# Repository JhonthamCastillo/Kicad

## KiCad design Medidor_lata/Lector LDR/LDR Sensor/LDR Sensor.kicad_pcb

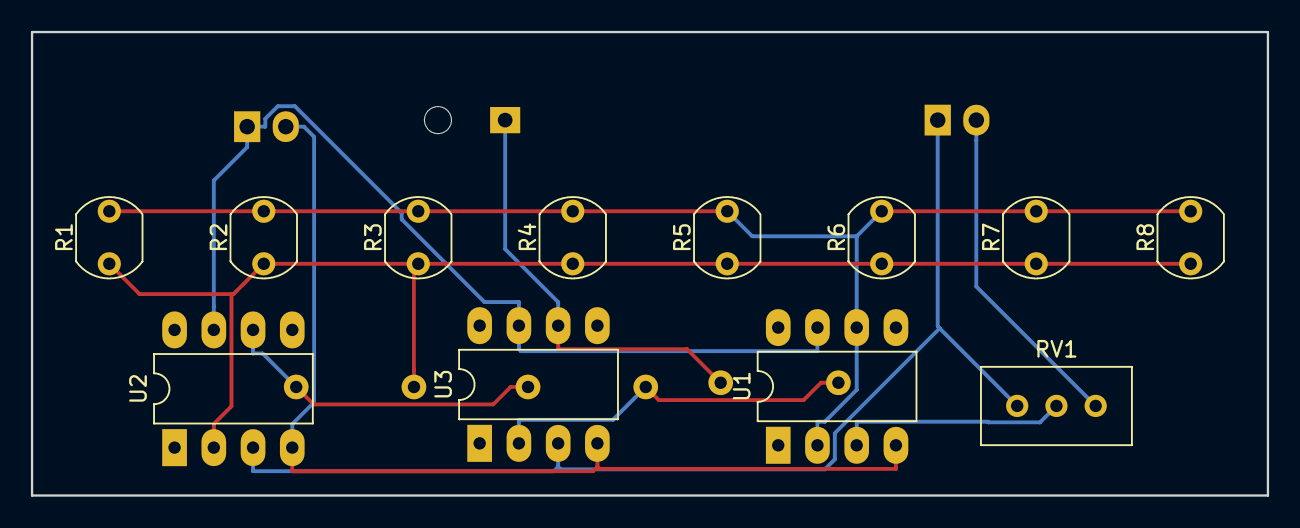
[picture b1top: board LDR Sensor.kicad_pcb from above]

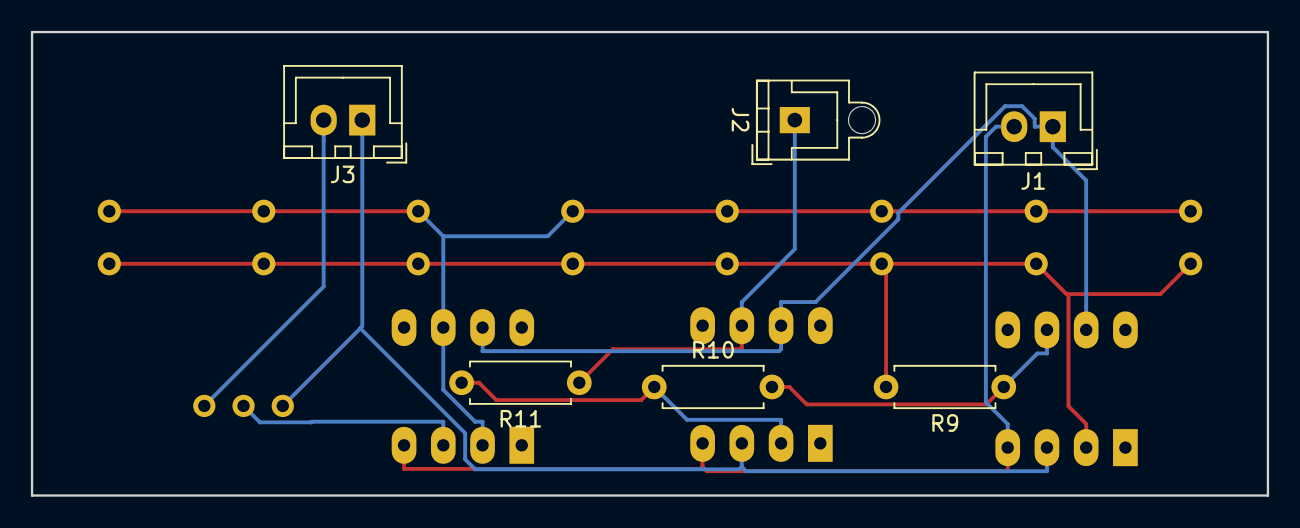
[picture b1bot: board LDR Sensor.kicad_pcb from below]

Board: 2 copper layers, 80.0 x 30.0 mm, 18 parts (6 on the bottom side), 10 nets.

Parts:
J1, J3: Conn_01x02_Female; JST_XH_B02B-XH-A_1x02_P2.50mm_Vertical
J2: Conn_01x01_Female; JST_XH_B01B-XH-AM_1x01_P2.50mm_Vertical
R1, R2, R3, R4, R5, R6, R7, R8: LDR03; R_LDR_5.1x4.3mm_P3.4mm_Vertical
R9: 1K; R_Axial_DIN0207_L6.3mm_D2.5mm_P7.62mm_Horizontal
R10, R11: 10k; R_Axial_DIN0207_L6.3mm_D2.5mm_P7.62mm_Horizontal
RV1: R_POT; Potentiometer_Bourns_3296W_Vertical
U1, U2, U3: LM741; DIP-8_W7.62mm_LongPads

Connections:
+3.7V: J3.2, RV1.1
-VCC: J1.2, U1.4, U2.4, U3.4
GND: J3.1, RV1.3, U2.3, U3.3
unnamed: J2.1, R11.1, U3.6
unnamed: R1.1, R2.1, R3.1, R4.1, R5.1, R6.1, R7.1, R8.1, R9.2, U2.2
unnamed: R1.2, R2.2, R3.2, R4.2, R5.2, R6.2, R7.2, R8.2, U1.2, U1.6
unnamed: R10.1, R11.2, U3.2
unnamed: R9.1, R10.2, U2.6
unnamed: RV1.2, U1.3
VCC: J1.1, U1.7, U2.7, U3.7

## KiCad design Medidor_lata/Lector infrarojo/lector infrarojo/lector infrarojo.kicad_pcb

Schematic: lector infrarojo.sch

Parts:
IF1, IF2, IF3, IF4, IF5, IF6, IF7: TCRT5000
J1, J2: Conn_01x02_Female; JST_XH_B03B-XH-AM_1x03_P2.50mm_Vertical
Q1, Q2, Q3, Q4, Q5, Q6, Q7: BC857; SOT-23
R1, R2, R3, R4, R5, R6, R7, R8, R9, R10, R11, R12, R13, R14, R15, R16, R17, R18, R19, R20, R21: R; R_0805_2012Metric

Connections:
unnamed: IF1.1, R1.2
unnamed: IF1.2, Q1.1 (B), R8.1
unnamed: IF1.3, IF1.4, IF2.3, IF2.4, IF3.3, IF3.4, IF4.3, IF4.4, IF5.3, IF5.4, IF6.3, IF6.4, IF7.3, IF7.4, J1.1, J2.1, R4.1, R5.1, R6.1, R7.1
unnamed: IF2.1, R2.2
unnamed: IF2.2, Q2.1 (B), R10.1
unnamed: IF3.1, R3.2
unnamed: IF3.2, Q3.1 (B), R12.1
unnamed: IF4.1, R4.2
unnamed: IF4.2, Q4.1 (B), R14.1
unnamed: IF5.1, R5.2
unnamed: IF5.2, Q5.1 (B), R16.1
unnamed: IF6.1, R6.2
unnamed: IF6.2, Q6.1 (B), R18.1
unnamed: IF7.1, R7.2
unnamed: IF7.2, Q7.1 (B), R20.1
unnamed: J1.2, J2.2, Q1.2 (E), Q2.2 (E), Q3.2 (E), Q4.2 (E), Q5.2 (E), Q6.2 (E), Q7.2 (E), R1.1, R2.1, R3.1, R8.2, R10.2, R12.2, R14.2, R16.2, R18.2, R20.2
unnamed: Q1.3 (C), R9.1
unnamed: Q2.3 (C), R11.1
unnamed: Q3.3 (C), R13.1
unnamed: Q4.3 (C), R15.1
unnamed: Q5.3 (C), R17.1
unnamed: Q6.3 (C), R19.1
unnamed: Q7.3 (C), R21.1
unnamed: R9.2, R11.2, R13.2, R15.2, R17.2, R19.2, R21.2

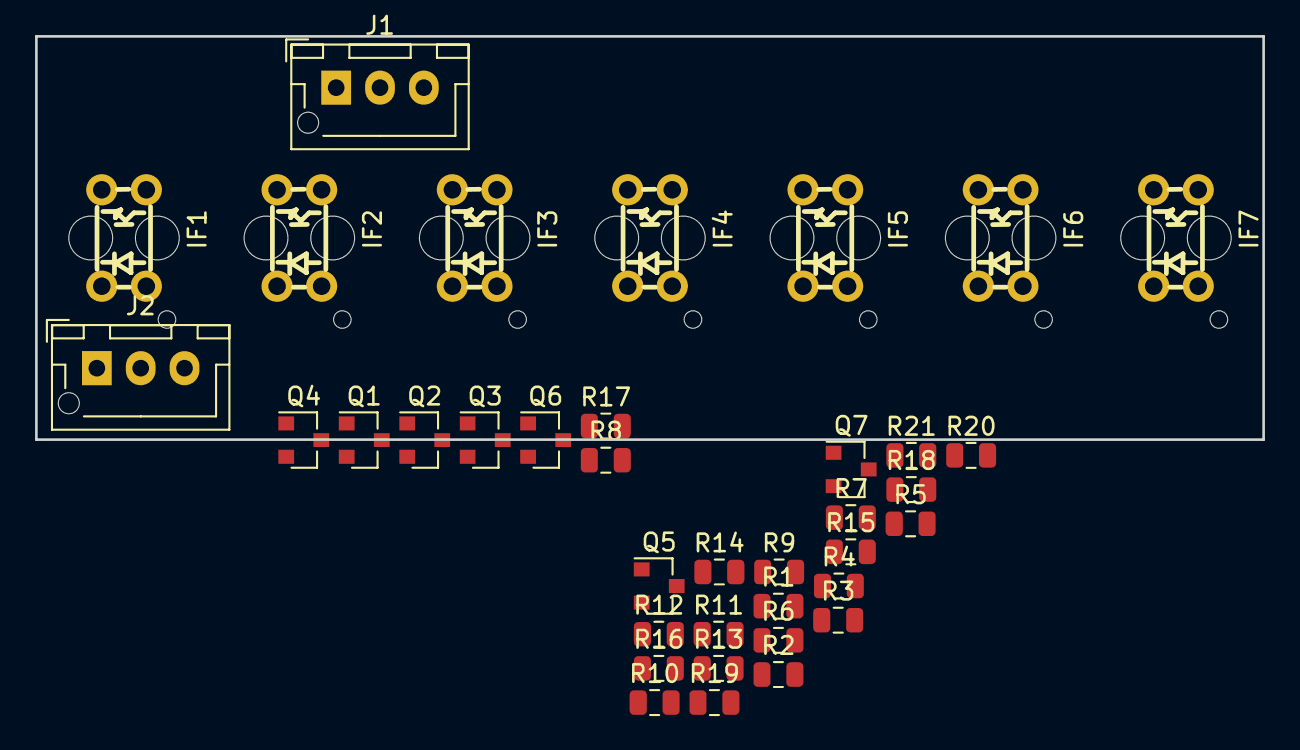
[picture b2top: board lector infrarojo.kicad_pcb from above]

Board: 2 copper layers, 70.0 x 23.0 mm, 37 parts (0 on the bottom side), 24 nets, no tracks yet.

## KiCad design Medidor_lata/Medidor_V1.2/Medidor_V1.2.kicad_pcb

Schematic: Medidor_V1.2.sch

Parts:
J1: Conn_01x02_Female; JST_EH_B02B-EH-A_1x02_P2.50mm_Vertical
J2: Conn_01x04_Female; JST_EH_B04B-EH-A_1x04_P2.50mm_Vertical
R1, R2, R3, R4, R5, R6, R7, R8, R9: R; R_0805_2012Metric
Sw1: Pulsador
U1: CC56-12EWA; 7segdisp8.0in4Dig
U2: ATmega328-AU; TQFP-32_7x7mm_P0.8mm

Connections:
+5V: J1.2, J2.1, R9.1, U2.4 (VCC), U2.6 (VCC)
GND: J1.1, J2.2, Sw1.2, U2.3 (GND), U2.5 (GND), U2.21 (GND)
unnamed: J2.3, U2.30 (PD0)
unnamed: J2.4, U2.31 (PD1)
unnamed: R1.1, U1.11
unnamed: R1.2, U2.16 (PB4)
unnamed: R2.1, U1.7
unnamed: R2.2, U2.17 (PB5)
unnamed: R3.1, U1.4
unnamed: R3.2, U2.32 (PD2)
unnamed: R4.1, U1.2
unnamed: R4.2, U2.1 (PD3)
unnamed: R5.1, U1.1
unnamed: R5.2, U2.2 (PD4)
unnamed: R6.1, U1.10
unnamed: R6.2, U2.9 (PD5)
unnamed: R7.1, U1.5
unnamed: R7.2, U2.10 (PD6)
unnamed: R8.1, U1.3
unnamed: R8.2, U2.11 (PD7)
unnamed: R9.2, Sw1.1, U2.29 (~RESET~/PC6)
unnamed: U1.6, U2.15 (PB3)
unnamed: U1.8, U2.14 (PB2)
unnamed: U1.9, U2.13 (PB1)
unnamed: U1.12, U2.12 (PB0)

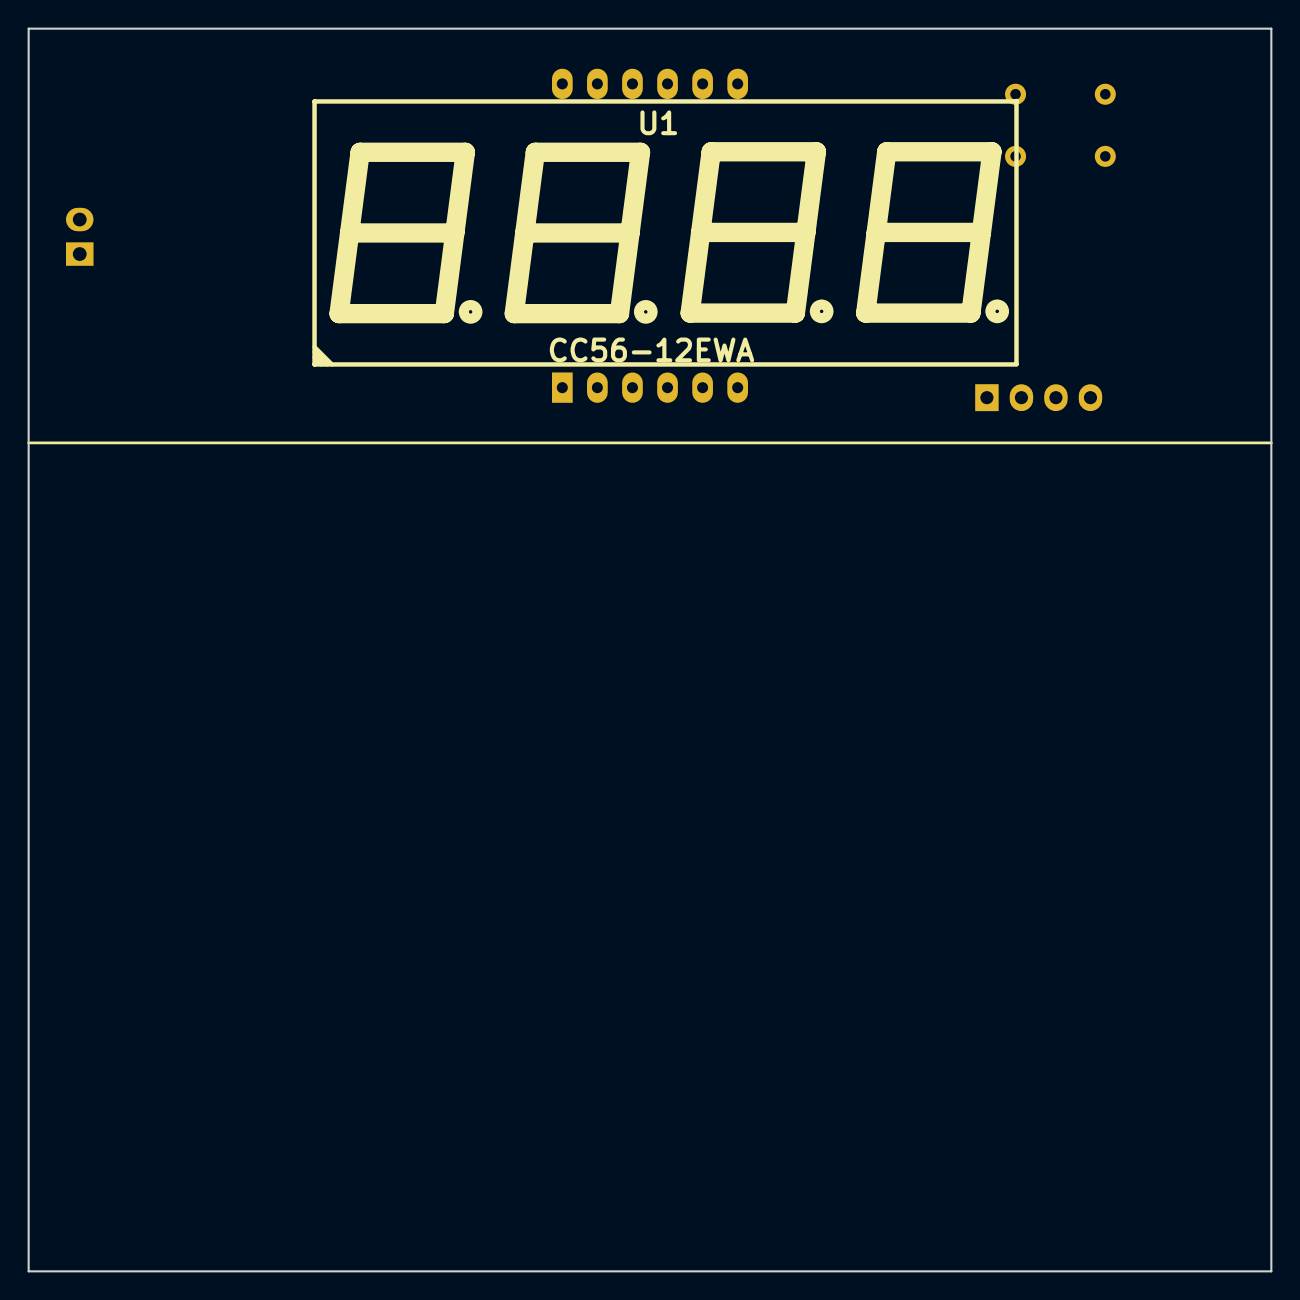
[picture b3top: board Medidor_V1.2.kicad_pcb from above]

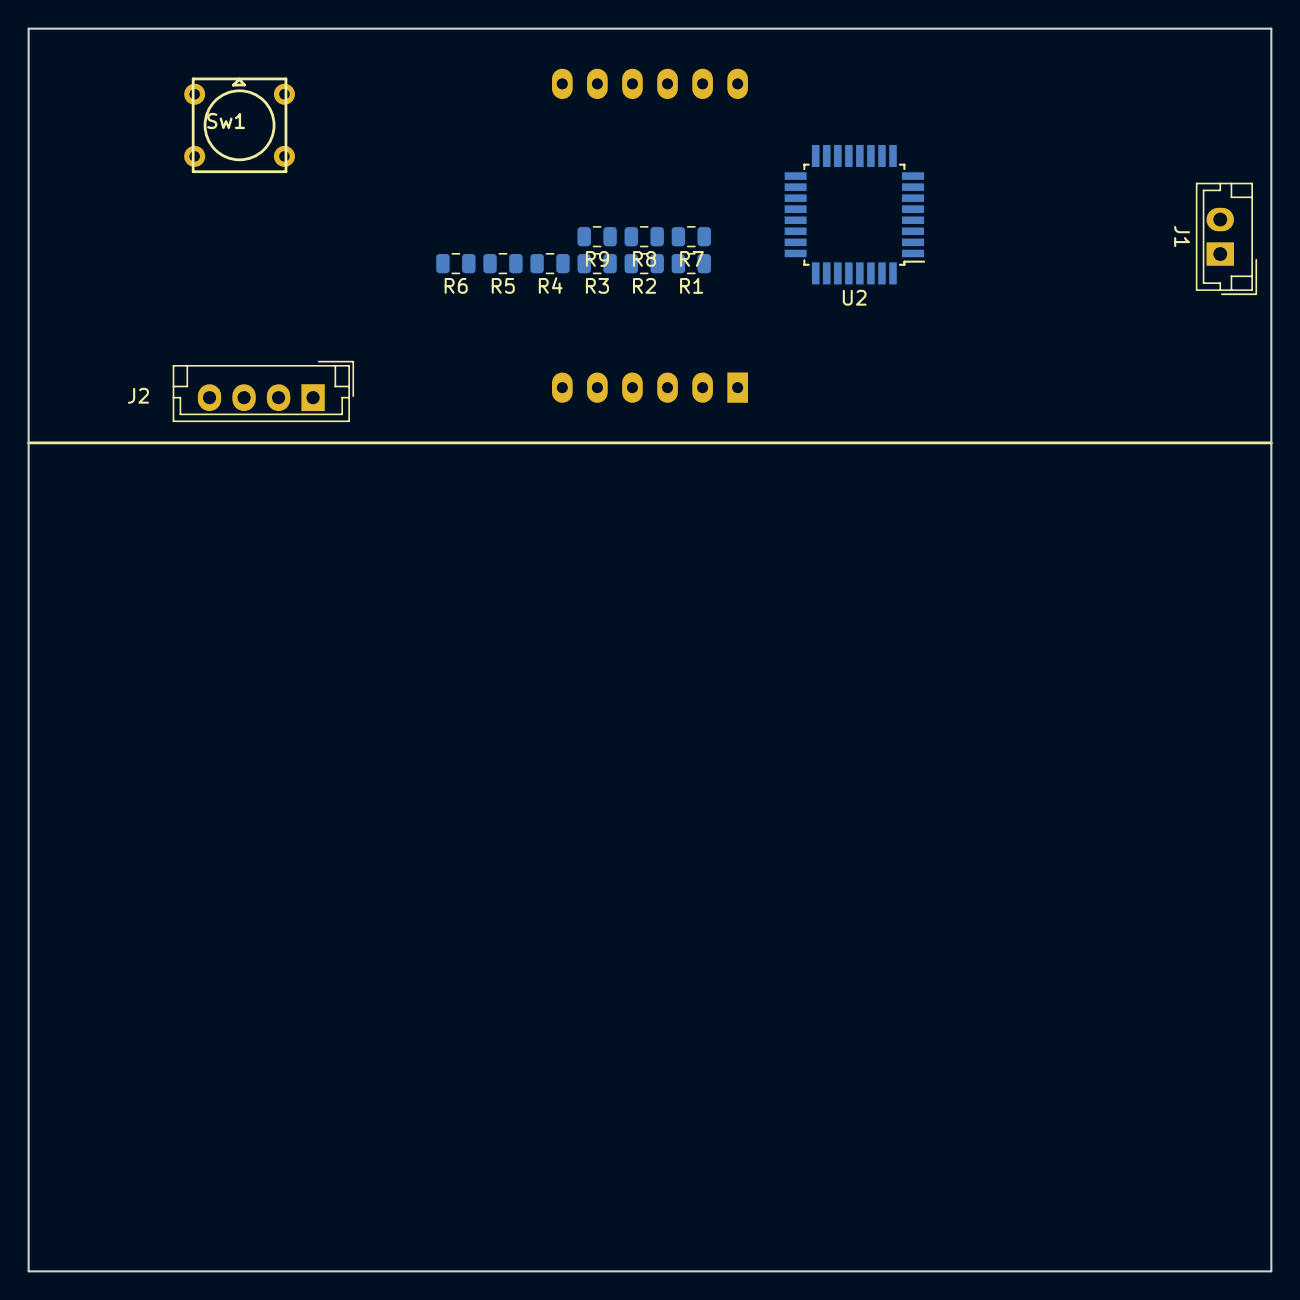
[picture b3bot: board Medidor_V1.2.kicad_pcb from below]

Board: 2 copper layers, 90.0 x 90.0 mm, 14 parts (13 on the bottom side), 25 nets, no tracks yet.

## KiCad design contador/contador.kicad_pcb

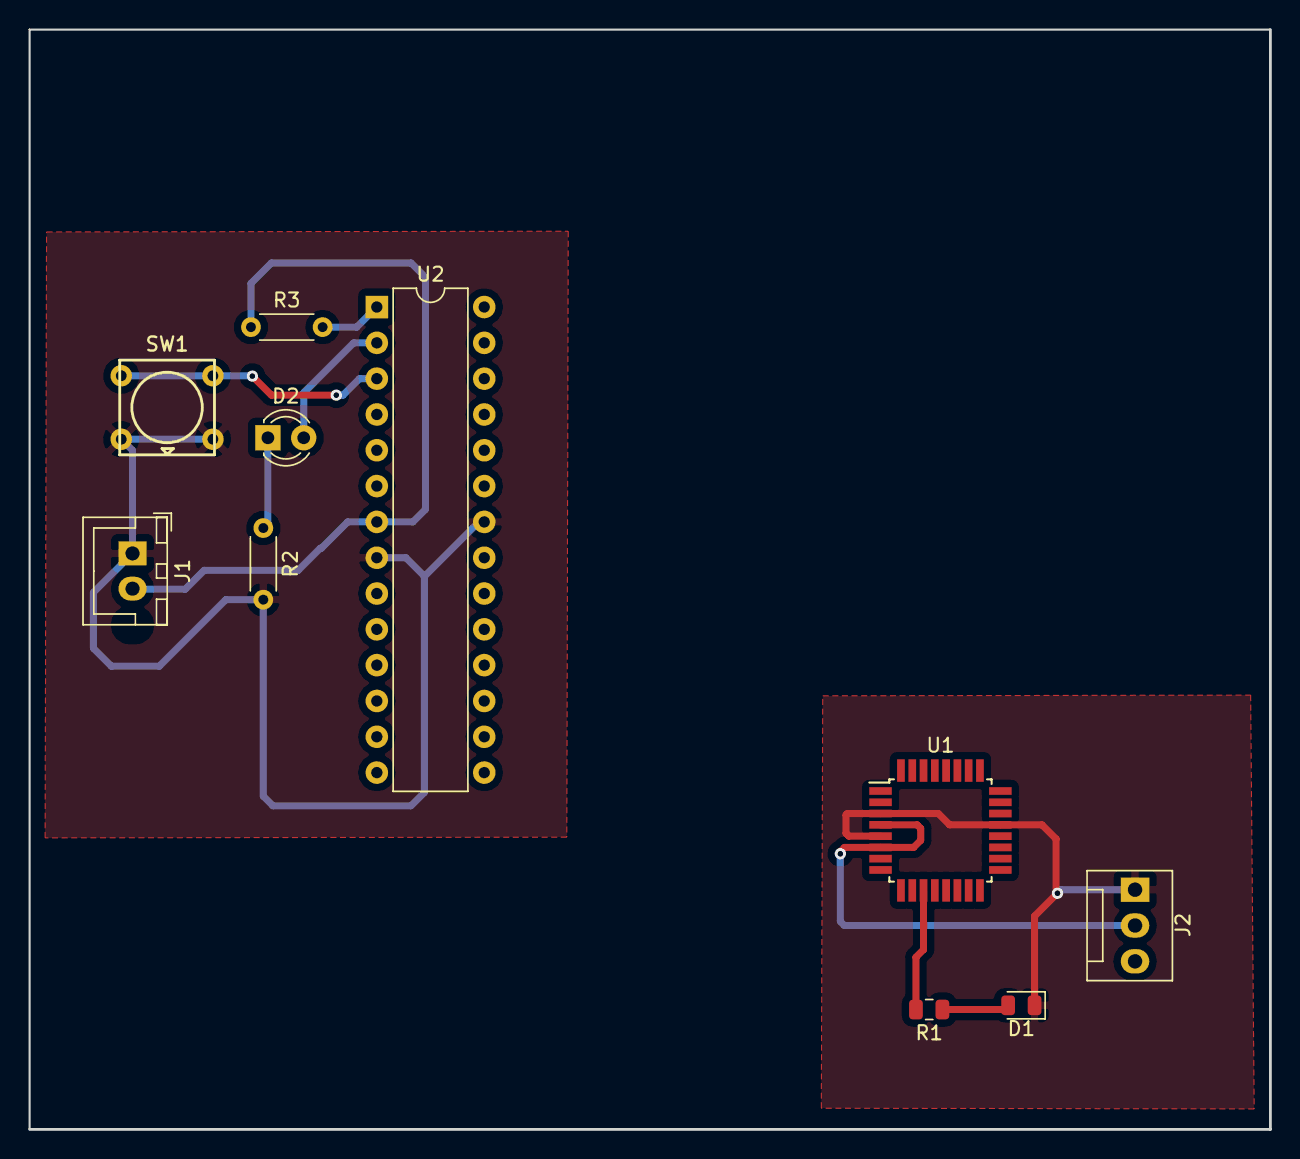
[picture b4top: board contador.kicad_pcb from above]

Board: 2 copper layers, 88.0 x 78.0 mm, 10 parts (0 on the bottom side), 8 nets.

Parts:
D1: LED; LED_0805_2012Metric
D2: LED; LED_D3.0mm
J1: Conn_01x02_Female; JST_XH_B02B-XH-A_1x02_P2.50mm_Vertical
J2: Conn_01x02_Female; FanPinHeader_1x03_P2.54mm_Vertical
R1: 361; R_0805_2012Metric
R2: 360; R_Axial_DIN0204_L3.6mm_D1.6mm_P5.08mm_Horizontal
R3: 1k; R_Axial_DIN0204_L3.6mm_D1.6mm_P5.08mm_Horizontal
SW1: Pulsador
U1: ATmega328-AU; TQFP-32_7x7mm_P0.8mm
U2: ATmega328-PU; DIP-28_W7.62mm

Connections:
+5V: J1.2, J2.2, R3.1, U1.4, U1.6, U2.7
GND: D1.1, J1.1, J2.1, R2.2, SW1.1, U1.3, U1.5, U1.21, U2.8, U2.22
unnamed: D1.2, R1.1
unnamed: D2.1, R2.1
unnamed: D2.2, U2.2
unnamed: R1.2, U1.11
unnamed: R3.2, U2.1
unnamed: SW1.2, U2.3

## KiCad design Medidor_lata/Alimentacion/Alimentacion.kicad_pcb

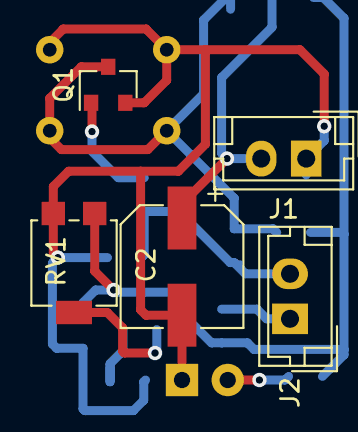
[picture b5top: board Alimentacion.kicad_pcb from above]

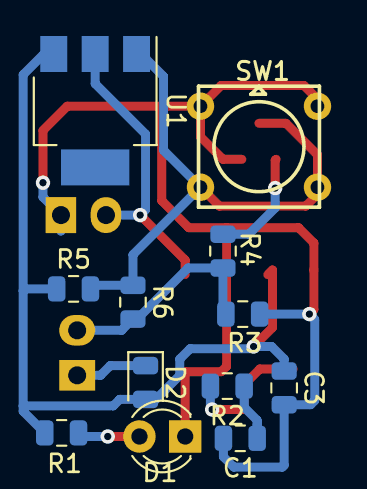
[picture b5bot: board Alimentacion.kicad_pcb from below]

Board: 2 copper layers, 17 parts (12 on the bottom side), 10 nets.

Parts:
C1, C3: C; C_0805_2012Metric
C2: CP; CP_Elec_6.3x7.7
D1: LED; LED_D3.0mm
D2: 1N4001; D_0805_2012Metric
J1, J2: Conn_01x02_Female; JST_EH_B02B-EH-A_1x02_P2.50mm_Vertical
Q1: BC847; SOT-23
R1, R2, R3, R4, R5, R6: R; R_0805_2012Metric
RV1: R_POT; Potentiometer_Bourns_3314G_Vertical
SW1: Pulsador
U1: LM317_TO3; SOT-223

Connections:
GND: C1.2, C2.2, C3.2, D1.1, J1.1, Q1.2, R3.2, RV1.3, SW1.1
unnamed: C1.1, R2.1
unnamed: C2.1, J1.2, U1.2
unnamed: C3.1, D2.2, R1.1, R5.1, RV1.1, U1.3
unnamed: D1.2, R1.2
unnamed: D2.1, J2.1
unnamed: J2.2, R3.1, R4.2, R6.2
unnamed: Q1.1, R4.1
unnamed: Q1.3, R5.2, R6.1, SW1.2, U1.1
unnamed: R2.2, RV1.2

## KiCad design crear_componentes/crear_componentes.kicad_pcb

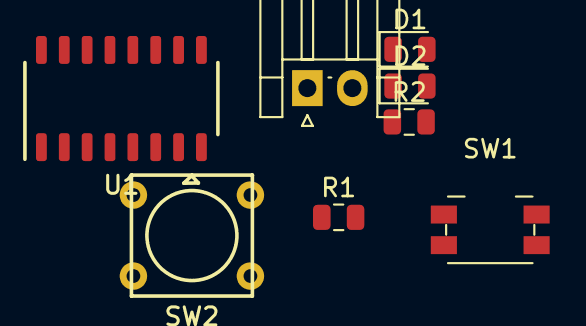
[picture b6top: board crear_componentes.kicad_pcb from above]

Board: 2 copper layers, 8 parts (0 on the bottom side), 7 nets, no tracks yet.

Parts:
D1, D2: LED; LED_0805_2012Metric
J1: Conn_01x02_Female; JST_EH_S02B-EH_1x02_P2.50mm_Horizontal
R1, R2: R; R_0805_2012Metric
SW1: SW_Push; Panasonic_EVQPUK_EVQPUB
SW2: TopPush
U1: ULN2003A; SOIC127P620X175-16

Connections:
+5V: J1.1, SW1.1, SW2.1, U1.8
GND: J1.2, R1.2, R2.2, U1.9
unnamed: D1.1, U1.16
unnamed: D1.2, R1.1
unnamed: D2.1, SW2.2
unnamed: D2.2, R2.1
unnamed: SW1.2, U1.1

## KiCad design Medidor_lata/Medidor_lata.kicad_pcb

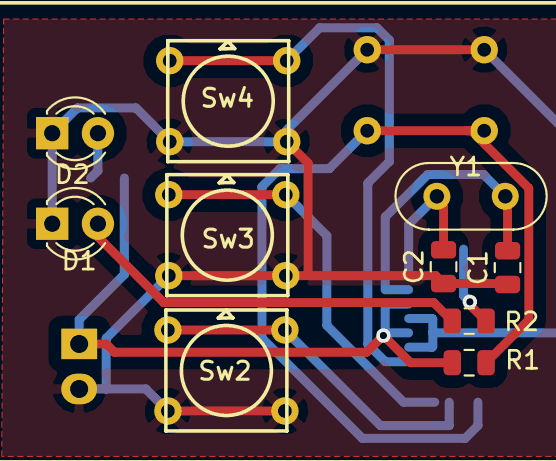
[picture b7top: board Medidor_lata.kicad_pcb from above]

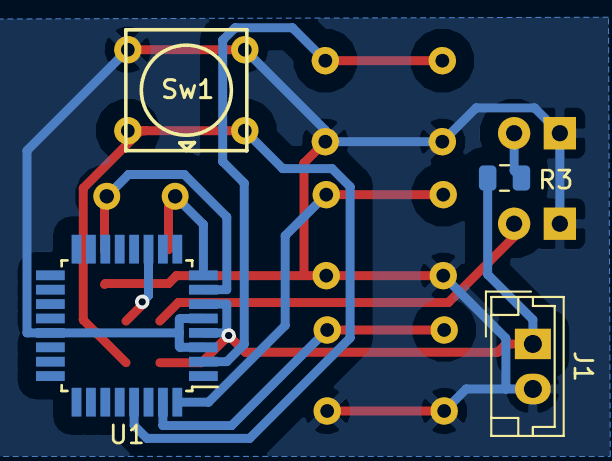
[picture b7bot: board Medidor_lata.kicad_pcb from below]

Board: 2 copper layers, 14 parts (4 on the bottom side), 11 nets.

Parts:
C1, C2: C; C_0805_2012Metric
D1, D2: LED; LED_D3.0mm
J1: Conn_01x02_Female; JST_EH_B02B-EH-A_1x02_P2.50mm_Vertical
R1, R2, R3: R; R_0805_2012Metric
Sw1, Sw2, Sw3, Sw4: Pulsador
U1: ATmega328P-AU; TQFP-32_7x7mm_P0.8mm
Y1: Crystal; Crystal_HC52-8mm_Vertical

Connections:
+5V: J1.1, R1.1, R3.2, U1.4, U1.6
GND: C1.1, C2.1, D1.1, D2.1, J1.2, Sw1.2, Sw2.2, Sw3.2, Sw4.2, U1.3, U1.5, U1.21
unnamed: C1.2, U1.7, Y1.1
unnamed: C2.2, U1.8, Y1.2
unnamed: D1.2, R2.1
unnamed: D2.2, R3.1
unnamed: R1.2, Sw1.1, U1.29
unnamed: R2.2, U1.11
unnamed: Sw2.1, U1.31
unnamed: Sw3.1, U1.32
unnamed: Sw4.1, U1.2

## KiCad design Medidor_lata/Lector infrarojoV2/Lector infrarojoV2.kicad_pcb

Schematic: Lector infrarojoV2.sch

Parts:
D1: LED; LED_D3.0mm
J1: Conn_01x02_Female; JWT_A3963_1x02_P3.96mm_Vertical
R1: R; R_Axial_DIN0204_L3.6mm_D1.6mm_P5.08mm_Vertical
U1: ATmega328-AU; TQFP-32_7x7mm_P0.8mm

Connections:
+5V: J1.2, U1.4 (VCC), U1.6 (VCC)
GND: D1.1, J1.1, U1.3 (GND), U1.5 (GND), U1.21 (GND)
unnamed: D1.2, R1.2
unnamed: R1.1, U1.23 (PC0)

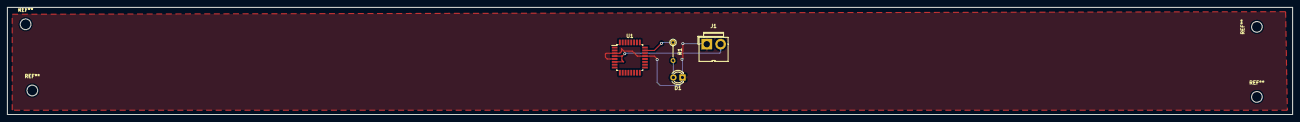
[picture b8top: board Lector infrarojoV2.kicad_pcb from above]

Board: 2 copper layers, 360.0 x 30.0 mm, 4 parts (0 on the bottom side), 4 nets.

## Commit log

2018-10-01 mis proyectos kicad
2018-10-02 desrrollo de circuito smd
2018-10-09 Hemos trabajado en nueva version de sistema de medicio
2018-11-05 Cambios de medidor
2019-01-20 actualizacion de kitkat
2019-02-14 Actualizacion
